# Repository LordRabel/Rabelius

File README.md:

# Rabelius
A compact full sized keyboard based on coseyfannitutti mysterium

I am currently working on my own keyboard.
I really am in love with 1800s but they are very rare. Thats why I designed this compact full size board. 
It has got 105 key and full ISO and ANSI support, aswell as a stepped Caps-key possibility.

I was verry inspired by coseyfannituttis mysterium, I just like seeing the components.
BIG THANKS to coseyfannitutti for making it an open project!!

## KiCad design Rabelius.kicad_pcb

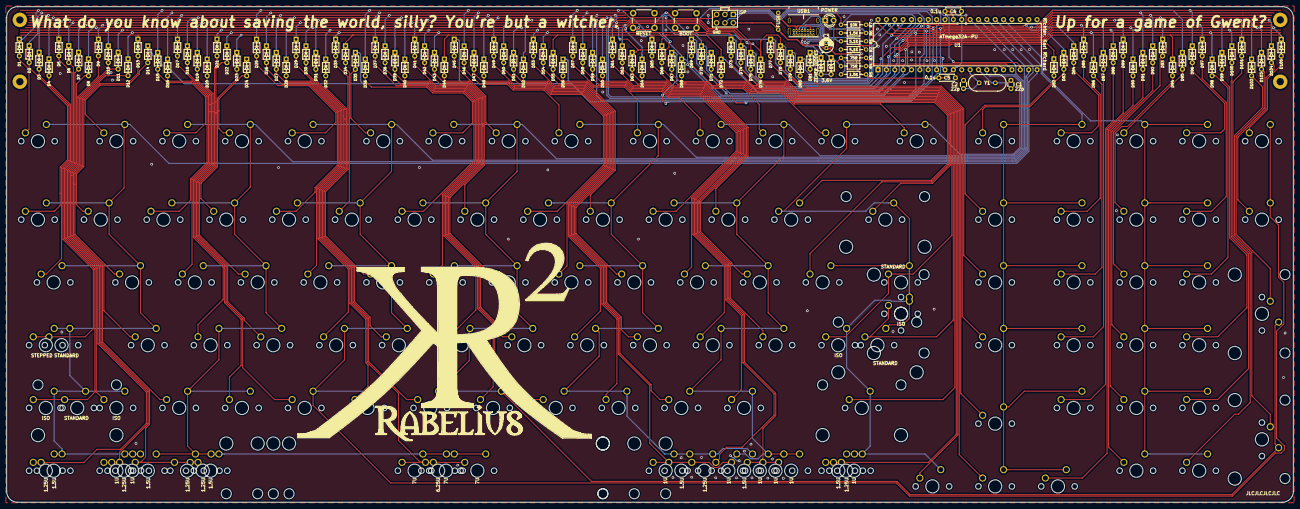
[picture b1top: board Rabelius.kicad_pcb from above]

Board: 2 copper layers, 390.5 x 150.4 mm, 257 parts (0 on the bottom side), 109 nets.

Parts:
BOOT1: BOOT; SW_PUSH_6mm
C1, C2: 22p; C_Disc_D3.0mm_W1.6mm_P2.50mm
C3: 4.7u; CP_Radial_D4.0mm_P1.50mm
C4, C5: 0.1u; C_Disc_D4.3mm_W1.9mm_P5.00mm
D1, D2, D3, D4, D5, D6, D7, D8, D9, D10, D11, D12, D13, D14, D15, D16, D17, D18, D19, D20, D21, D22, D23, D24, D25, D26, D27, D28, D29, D30, D31, D32, D33, D34, D35, D36, D37, D38, D39, D40, D41, D42, D43, D44, D45, D46, D47, D48, D49, D50, D51, D52, D53, D54, D55, D56, D57, D58, D59, D60, D61, D62, D63, D64, D65, D66, D67, D68, D69, D70, D71, D72, D73, D74, D75, D76, D77, D78, D79, D80, D81, D82, D83, D84, D85, D86, D87, D88, D89, D90, D91, D92, D93, D94, D95, D96, D97, D98, D99, D100, D101, D102, D103, D104, D105: D_Small; D_DO-35_SOD27_P5.08mm_Horizontal
D95#2, D96#2: 3.6V; D_DO-35_SOD27_P5.08mm_Horizontal
F1: 500mA; polyfuse_5.1mm
J1: AVR-ISP-6; AVR_ICSP_3x2
LED1: POWER; LED_D3.0mm
R1, R2: 5.1K; R_Axial_DIN0204_L3.6mm_D1.6mm_P7.62mm_Horizontal
R3, R4: 75R; R_Axial_DIN0204_L3.6mm_D1.6mm_P7.62mm_Horizontal
R5, R6: 1.5K; R_Axial_DIN0204_L3.6mm_D1.6mm_P7.62mm_Horizontal
R7: 10K; R_Axial_DIN0204_L3.6mm_D1.6mm_P7.62mm_Horizontal
RESET1: RESET; SW_PUSH_6mm
ST83: 6.25U; MX-6.25U-Stabilizer
ST84, ST84#2, ST84#3: 7U; MX-7U-Stabilizer
SW0, SW1, SW2, SW3, SW4, SW5, SW6, SW7, SW8, SW9, SW10, SW11, SW12, SW13, SW13#2, SW13#3, SW13#4, SW13#5, SW13#6, SW13#7, SW13#8, SW13#9, SW13#10, SW13#11, SW13#12, SW13#13, SW13#14, SW13#15, SW13#16, SW13#17, SW13#18, SW13#19, SW13#20, SW13#21, SW14, SW16, SW17, SW18, SW19, SW20, SW21, SW22, SW23, SW24, SW25, SW26, SW27, SW28, SW30, SW32, SW34, SW35, SW36, SW37, SW38, SW39, SW40, SW41, SW42, SW43, SW44, SW45, SW47, SW49, SW52, SW53, SW54, SW55, SW56, SW57, SW58, SW59, SW59#2, SW60, SW60#2, SW61, SW61#2, SW62, SW62#2, SW65, SW66, SW67, SW68, SW69, SW70, SW71, SW72, SW73, SW74, SW74#2, SW76, SW80, SW80#2, SW80#3, SW83, SW84, SW84#2, SW84#3, SW89, SW92, SW93, SW94: KEYSW; SW_Cherry_MX1A_1.00u_PCB-NOSCREEN
SW29, SW29#2, SW29#3, SW29#4: KEYSW; SW_Cherry_MX1A_2.00u_PCBNOSCREEN
SW33, SW46, SW77, SW81, SW86, SW86#2, SW86#3, SW90: KEYSW; SW_Cherry_MX1A_1.50u_PCBNOSCREEN
SW50: KEYSW; SW_Cherry_MX1A_1.75u_PCBNOSCREEN
SW51, SW78, SW78#2, SW78#3, SW79, SW82, SW82#2, SW82#3: KEYSW; SW_Cherry_MX1A_1.25u_PCBNOSCREEN
SW63, SW64: KEYSW; SW_Cherry_MX1A_2.25u_PCBNOSCREEN
SW75: KEYSW; SW_Cherry_MX1A_2.75u_PCB_NOSCREEN
U1: ATmega32A-PU; DIP-40_W15.24mm
USB1: USB_C_GCT_USB4085
Y1: Crystal; Crystal_HC49-4H_Vertical

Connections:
+5V: C3.1, C4.1, C5.1, F1.1, J1.2, LED1.2, R5.1, R7.1, U1.10, U1.30
D+: R4.1, U1.16
D-: R3.1, U1.17
GND: BOOT1.1, C1.2, C2.2, C3.2, C4.2, C5.2, D95#2.2, D96#2.2, J1.6, R1.1, R2.2, R6.2, RESET1.1, U1.11, U1.31, USB1.A1, USB1.A12, USB1.B1, USB1.B12, USB1.S1
MISO: J1.1, U1.7
MOSI: J1.4, U1.6
unnamed: C1.1, U1.13, Y1.1
unnamed: C2.1, U1.12, Y1.2
unnamed: D1.2, SW0.2
unnamed: D14.2, SW1.2
unnamed: D15.2, SW2.2
unnamed: D24.2, SW3.2
unnamed: D25.2, SW4.2
unnamed: D35.2, SW5.2
unnamed: D36.2, SW6.2
unnamed: D45.2, SW7.2
unnamed: D46.2, SW8.2
unnamed: D56.2, SW9.2
unnamed: D57.2, SW10.2
unnamed: D67.2, SW11.2
unnamed: D68.2, SW12.2
unnamed: D83.2, SW14.2
unnamed: D2.2, SW16.2
unnamed: D13.2, SW17.2
unnamed: D16.2, SW18.2
unnamed: D23.2, SW19.2
unnamed: D26.2, SW20.2
unnamed: D34.2, SW21.2
unnamed: D37.2, SW22.2
unnamed: D44.2, SW23.2
unnamed: D47.2, SW24.2
unnamed: D55.2, SW25.2
unnamed: D58.2, SW26.2
unnamed: D66.2, SW27.2
unnamed: D70.2, SW28.1
unnamed: D72.2, SW29#4.2
unnamed: D82.2, SW30.2
unnamed: D81.2, SW32.2
unnamed: D3.2, SW33.2
unnamed: D12.2, SW34.2
unnamed: D17.2, SW35.2
unnamed: D22.2, SW36.2
unnamed: D27.2, SW37.2
unnamed: D33.2, SW38.2
unnamed: D38.2, SW39.2
unnamed: D43.2, SW40.2
unnamed: D48.2, SW41.2
unnamed: D54.2, SW42.2
unnamed: D59.2, SW43.2
unnamed: D65.2, SW44.2
unnamed: D71.2, SW45.2
unnamed: D73.2, SW13.2, SW46.2
unnamed: D69.2, SW47.2
unnamed: D80.2, SW49.2
unnamed: D4.2, SW50.2, SW51.2
unnamed: D11.2, SW52.2
unnamed: D18.2, SW53.2
unnamed: D21.2, SW54.2
unnamed: D28.2, SW55.2
unnamed: D32.2, SW56.2
unnamed: D39.2, SW57.2
unnamed: D42.2, SW58.2
unnamed: D49.2, SW59#2.2
unnamed: D53.2, SW60#2.2
unnamed: D60.2, SW61#2.2
unnamed: D64.2, SW62#2.2
unnamed: D74.2, SW13#2.2, SW63.2
unnamed: D5.2, SW64.2, SW78#2.2
unnamed: D6.2, SW65.2
unnamed: D10.2, SW66.2
unnamed: D19.2, SW67.2
unnamed: D20.2, SW68.2
unnamed: D29.2, SW69.2
unnamed: D31.2, SW70.2
unnamed: D40.2, SW71.2
unnamed: D41.2, SW72.2
unnamed: D50.2, SW73.2
unnamed: D52.2, SW74#2.2
unnamed: D75.2, SW75.2
unnamed: D79.2, SW76.2
unnamed: D7.2, SW77.2, SW78#3.2
unnamed: D8.2, SW79.2, SW80#2.2, SW80#3.2
unnamed: D9.2, SW81.2, SW82#2.2, SW82#3.2, SW86.2
unnamed: D30.2, SW83.2, SW84.2, SW84#2.2, SW84#3.2
unnamed: D51.2, SW59.2, SW78.2, SW86#2.2, SW86#3.2
unnamed: D62.2, SW60.2
unnamed: D63.2, SW61.2, SW80.2, SW89.2
unnamed: D76.2, SW62.2, SW82.2, SW90.2
unnamed: D77.2, SW92.2
unnamed: D78.2, SW93.2
unnamed: D89.2, SW94.2
unnamed: D95#2.1, R3.2, R5.2, USB1.A7, USB1.B7
unnamed: D96#2.1, R4.2, USB1.A6, USB1.B6
unnamed: LED1.1, R6.1
unnamed: R1.2, USB1.A5
unnamed: R2.1, USB1.B5
SCK: J1.3, U1.8
VCC: F1.2, USB1.A4, USB1.A9, USB1.B4, USB1.B9
boot: BOOT1.2, U1.18
col0: SW0.1, SW1.1, SW16.1, SW17.1, SW33.1, SW34.1, SW50.1, SW51.1, SW52.1, SW64.1, SW65.1, SW77.1, SW78#2.1, SW78#3.1, SW79.1, SW80#2.1, SW80#3.1, U1.20
col1: SW2.1, SW3.1, SW18.1, SW19.1, SW35.1, SW36.1, SW53.1, SW54.1, SW66.1, SW67.1, SW81.1, SW82#2.1, SW82#3.1, SW83.1, SW84.1, SW84#2.1, SW84#3.1, SW86.1, U1.27
col2: SW4.1, SW5.1, SW13#14.1, SW13#15.1, SW20.1, SW21.1, SW37.1, SW38.1, SW55.1, SW56.1, SW68.1, SW69.1, U1.19
col3: SW6.1, SW7.1, SW22.1, SW23.1, SW29#2.1, SW29#3.1, SW39.1, SW40.1, SW57.1, SW58.1, SW70.1, SW71.1, U1.28
col4: SW8.1, SW9.1, SW24.1, SW25.1, SW41.1, SW42.1, SW59.1, SW59#2.1, SW60#2.1, SW72.1, SW73.1, SW78.1, SW86#2.1, SW86#3.1, U1.29
col5: SW10.1, SW11.1, SW26.1, SW27.1, SW43.1, SW44.1, SW60.1, SW61.1, SW61#2.1, SW62#2.1, SW74.1, SW74#2.1, SW80.1, SW89.1, U1.15
col6: SW12.1, SW13.1, SW13#2.1, SW28.2, SW29.2, SW29#4.1, SW45.1, SW46.1, SW47.1, SW62.1, SW63.1, SW75.1, SW82.1, SW90.1, SW92.1, U1.14
col7: SW13#7.1, SW13#8.1, SW13#13.1, SW13#20.1, SW13#21.1, SW14.1, SW30.1, SW32.1, SW49.1, SW76.1, SW93.1, SW94.1, U1.26
col8: SW13#3.1, SW13#4.1, SW13#5.1, SW13#6.1, SW13#9.1, SW13#10.1, SW13#11.1, SW13#12.1, SW13#16.1, SW13#17.1, SW13#18.1, SW13#19.1, U1.25
reset: J1.5, R7.2, RESET1.2, U1.9
